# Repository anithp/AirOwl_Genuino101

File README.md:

# AirOwl_Genuino101
Board files and code for Airowl.
Airowl is the device that measures air quality and lets you know what you breath.
For knowing more about Airowl please visit :- https://goo.gl/TVHfYz

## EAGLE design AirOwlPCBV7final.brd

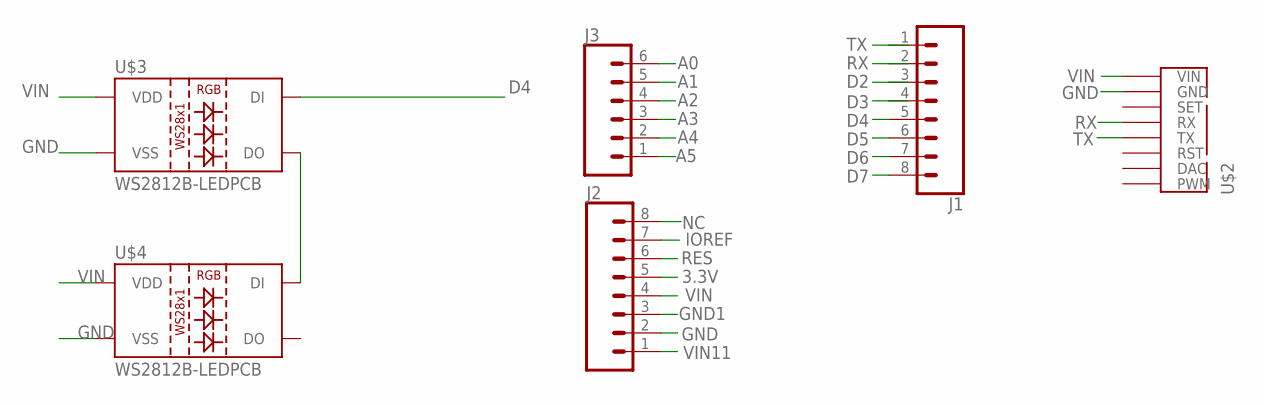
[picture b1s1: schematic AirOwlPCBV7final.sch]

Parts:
J1, J2: CONN_08"; 1X08
J3: CONN_06SILK_FEMALE_PTH; 1X06
U$2: WINSEN_CONNECTOR
U$3, U$4: WS2812B-LEDPCB

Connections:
3.3V: J2.5
A0: J3.6
A1: J3.5
A2: J3.4
A3: J3.3
A4: J3.2
A5: J3.1
D2: J1.3
D3: J1.4
D4: J1.5, U$3.4 (DI)
D5: J1.6
D6: J1.7
D7: J1.8
GND: J2.2, U$2.P$8 (GND), U$3.3 (VSS), U$4.3 (VSS)
GND1: J2.3
IOREF: J2.7
unnamed: U$3.2 (DO), U$4.4 (DI)
NC: J2.8
RES: J2.6
RX: J1.2, U$2.P$6 (RX)
TX: J1.1, U$2.P$5 (TX)
VIN: J2.4, U$2.P$9 (VIN), U$3.1 (VDD), U$4.1 (VDD)
VIN11: J2.1

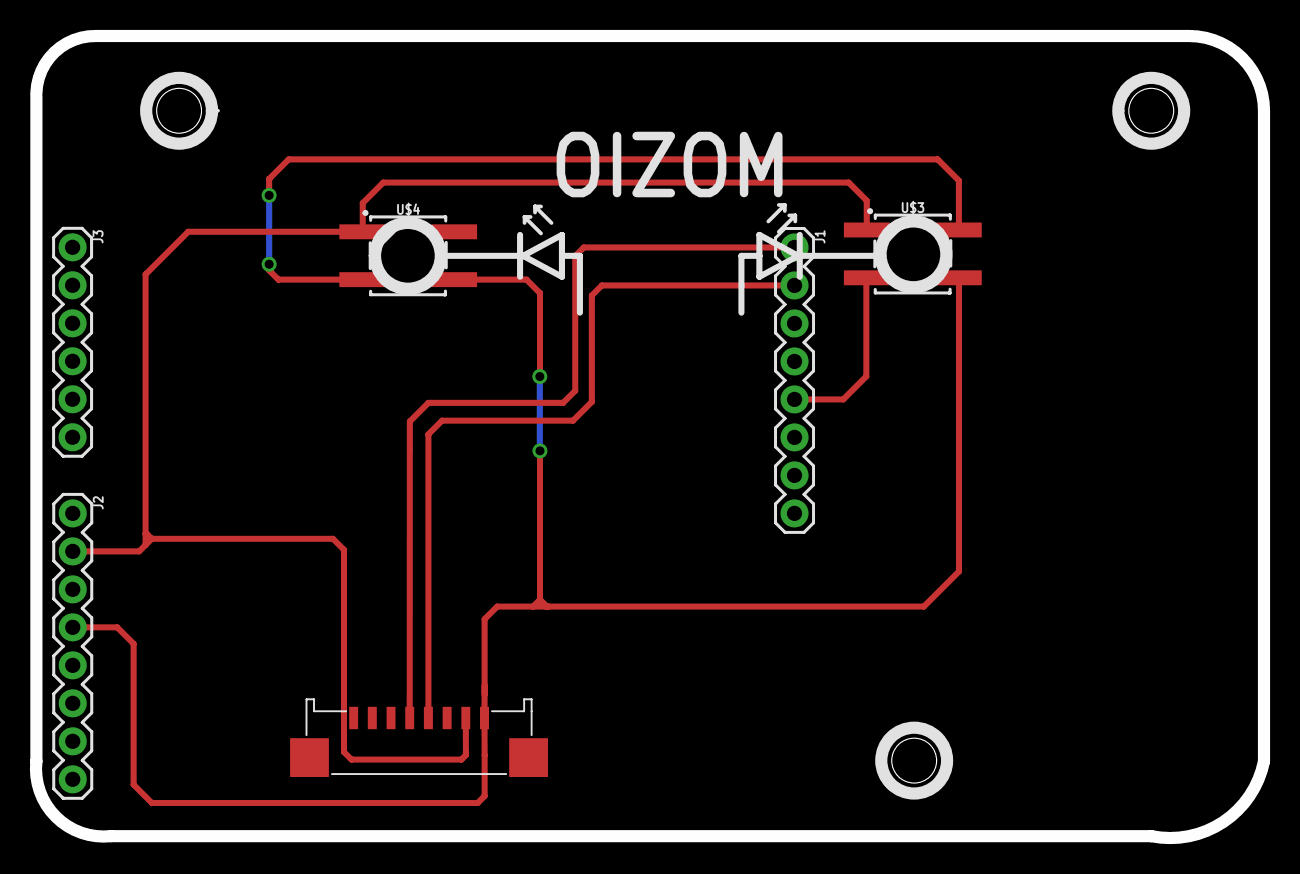
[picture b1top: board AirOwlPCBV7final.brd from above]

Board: 2 copper layers, 82.1 x 53.6 mm, 7 parts (0 on the bottom side), 6 nets.

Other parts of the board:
U$5: AIROWLPCB-LIB

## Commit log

2017-07-03 Create Code
2017-07-03 Rename Code to code.c
2018-06-18 PWM Sensor

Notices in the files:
parts and their libraries:
SparkFun-Connectors: Licensing: Creative Commons ShareAlike 4.0 International - https://creativecommons.org/licenses/by-sa/4.0
